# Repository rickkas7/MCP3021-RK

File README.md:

# MCP3021-RK

*Particle library for MCP3021 I2C 10-bit ADC*

I'm not sure why you'd need this, as the Particle Photon and Electron already have a lot of ADC inputs. I originally did this because I thought I might need an ADC at the end of a long-range I2C bus, but you never know when you might need it so here it is.

The Microchip MCP3021 is a tiny (SOT-23-5), inexpensive (US$1.12 in single quantities) 10-bit ADC with an I2C interface. It operates on from 2.7V to 5.5V, which can also be handy.

I got mine from [Digikey](https://www.digikey.com/product-detail/en/microchip-technology/MCP3021A5T-E-OT/MCP3021A5T-E-OTCT-ND/1979808) but they're widely available.

One issue is that it's only available in the SMT SOT-23-5 package, so it's intended to be included directly on your board. For prototyping, you could use a SOT-23-5 breakout, or build your own. 

I built a tiny circuit board for this purpose that contains the chip and two I2C pull-up resistors. The Eagle CAD schematic and layout are included in the eagle directory.

This ADC is fast - it samples during the I2C transaction, so you can call it as often as you want.

## Sample program

Here's a simple sample program to read the ADC:

```
#include "Particle.h"

#include "MCP3021-RK.h"

const unsigned long SAMPLE_PERIOD_MS = 1000;

MCP3021 adc(Wire);
bool haveChip = false;
unsigned long lastSample = 0;

void setup() {
	Serial.begin(9600);
	adc.begin();
}

void loop() {
	if (millis() - lastSample >= SAMPLE_PERIOD_MS) {
		lastSample = millis();

		if (!haveChip) {
			haveChip = adc.check();
			Serial.printlnf("haveChip=%d", haveChip);
		}
		if (haveChip) {
			Serial.printlnf("value=%u", adc.getSample());
		} else {
			Serial.println("no MCP3021 detected");
		}
	}
}

```

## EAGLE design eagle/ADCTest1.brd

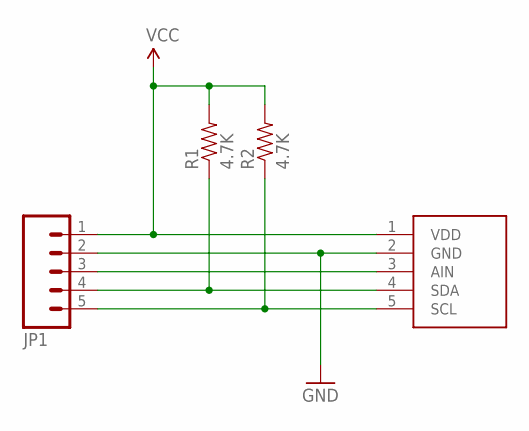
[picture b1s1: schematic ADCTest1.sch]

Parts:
JP1: M05PTH; 1X05
R1, R2: 4.7K; 0603-RES
U$1: MCP3021-ADC; SOT-23-5-MICROCHIP

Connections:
GND: JP1.2, U$1.2 (GND)
unnamed: JP1.3, U$1.3 (AIN)
unnamed: JP1.4, R1.1, U$1.4 (SDA)
unnamed: JP1.5, R2.1, U$1.5 (SCL)
VCC: JP1.1, R1.2, R2.2, U$1.1 (VDD)

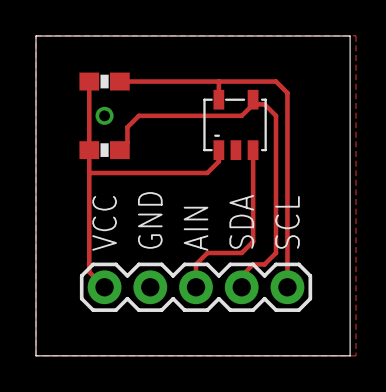
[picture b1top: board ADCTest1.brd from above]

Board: 2 copper layers, 17.4 x 17.8 mm, 4 parts (0 on the bottom side), 5 nets.

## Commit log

2017-10-07 initial checkin
